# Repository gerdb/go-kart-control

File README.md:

#Go-Kart Control  
####Radio controlled displays for go-kart tracks  
---

##Install the Go-Kart-Control software
Download and unzip the ZIP archive containing all executables and also the source code:  
https://github.com/gerdb/go-kart-control/archive/master.zip  
On a windows system just start the executable **Go-Kart-Control.exe** in /install/win32 or win64  
On a Mac or Linux start the java JAR archive in install/all with **java - jar go-kart-control.jar**.  
Don't forget to set the correct serial port in settings.txt.  
Java must be installed: https://www.java.com/de/download/  

##Translation
You can translate the application.  
Open the *lang/messages.pot* file and translate it with http://poedit.net/  
Save the *messages_LANGUAGE_CODE.po* file in the *lang* folder of your program.  
Set the local code in *settings.txt*, if you don't want to use the system settings.

##Arduino software
If it's a new AVR, program it with the Arduino bootloader. For example with AVRDUDE:  
`avrdude -pm32u4 -cstk500 -P/dev/ttyUSB0 -e`  
`avrdude -pm32u4 -cstk500 -P/dev/ttyUSB0 -v -e -U lfuse:w:0xff:m -U hfuse:w:0xd8:m -U efuse:w:0xcb:m`  
`avrdude -pm32u4 -cstk500 -P/dev/ttyUSB0 -v -e -U flash:w:Caterina-Micro.hex -U lock:w:0x2F:m`

The Arduino project file is: **arduino/go_kart_panel/go_kart_panel.ino**

##Hardware setup
The PCB can be assembles in 2 variants: As a master module or as a panel module.  
The master module is connected to the PC.  
The panel module has a display.
The differences between both electronics are marked here:  

###PCB layout

###Master module
The master module is connected to a USB port of a PC or notebook. The master module can be supplied by USB or by an external 12V power supply. An external power supply is recommended on high power settings (If not, the blue LED is flickering). 

###Panel module
If there is a new master module, update the radio.ino file with the master's XBee address and download it to all panel modules. The panels will only accept data from this master.   
On startup, the software version, the battery voltage (120=12V) and the power setting (0..4) is displayed.  
The XBee module is ready when all LEDs blink for a short time.  
If then the testpoint P11 and P12 are connected together, the module displays the XBee address step by step and a display test is performed. Use this address to update the **settings.txt**  

Use 7-segment displays with common anode. Voltage is 12V. Use external resistors in each line **a**..**g**  
Connect LEDs to display the flag status. Connect the anode together.  
The maximum current for 7-segment display or LED is 300mA per line.

##Your own Go-Kart track
You can use the /pics/track.svg to generate you own background images for your go-kart tracks.  
Edit this with Inkscape https://inkscape.org/de/ and export it as bitmap to your /pics folder. Filename is background.png.  
Edit the settings.txt and change the x and y position of your panels.

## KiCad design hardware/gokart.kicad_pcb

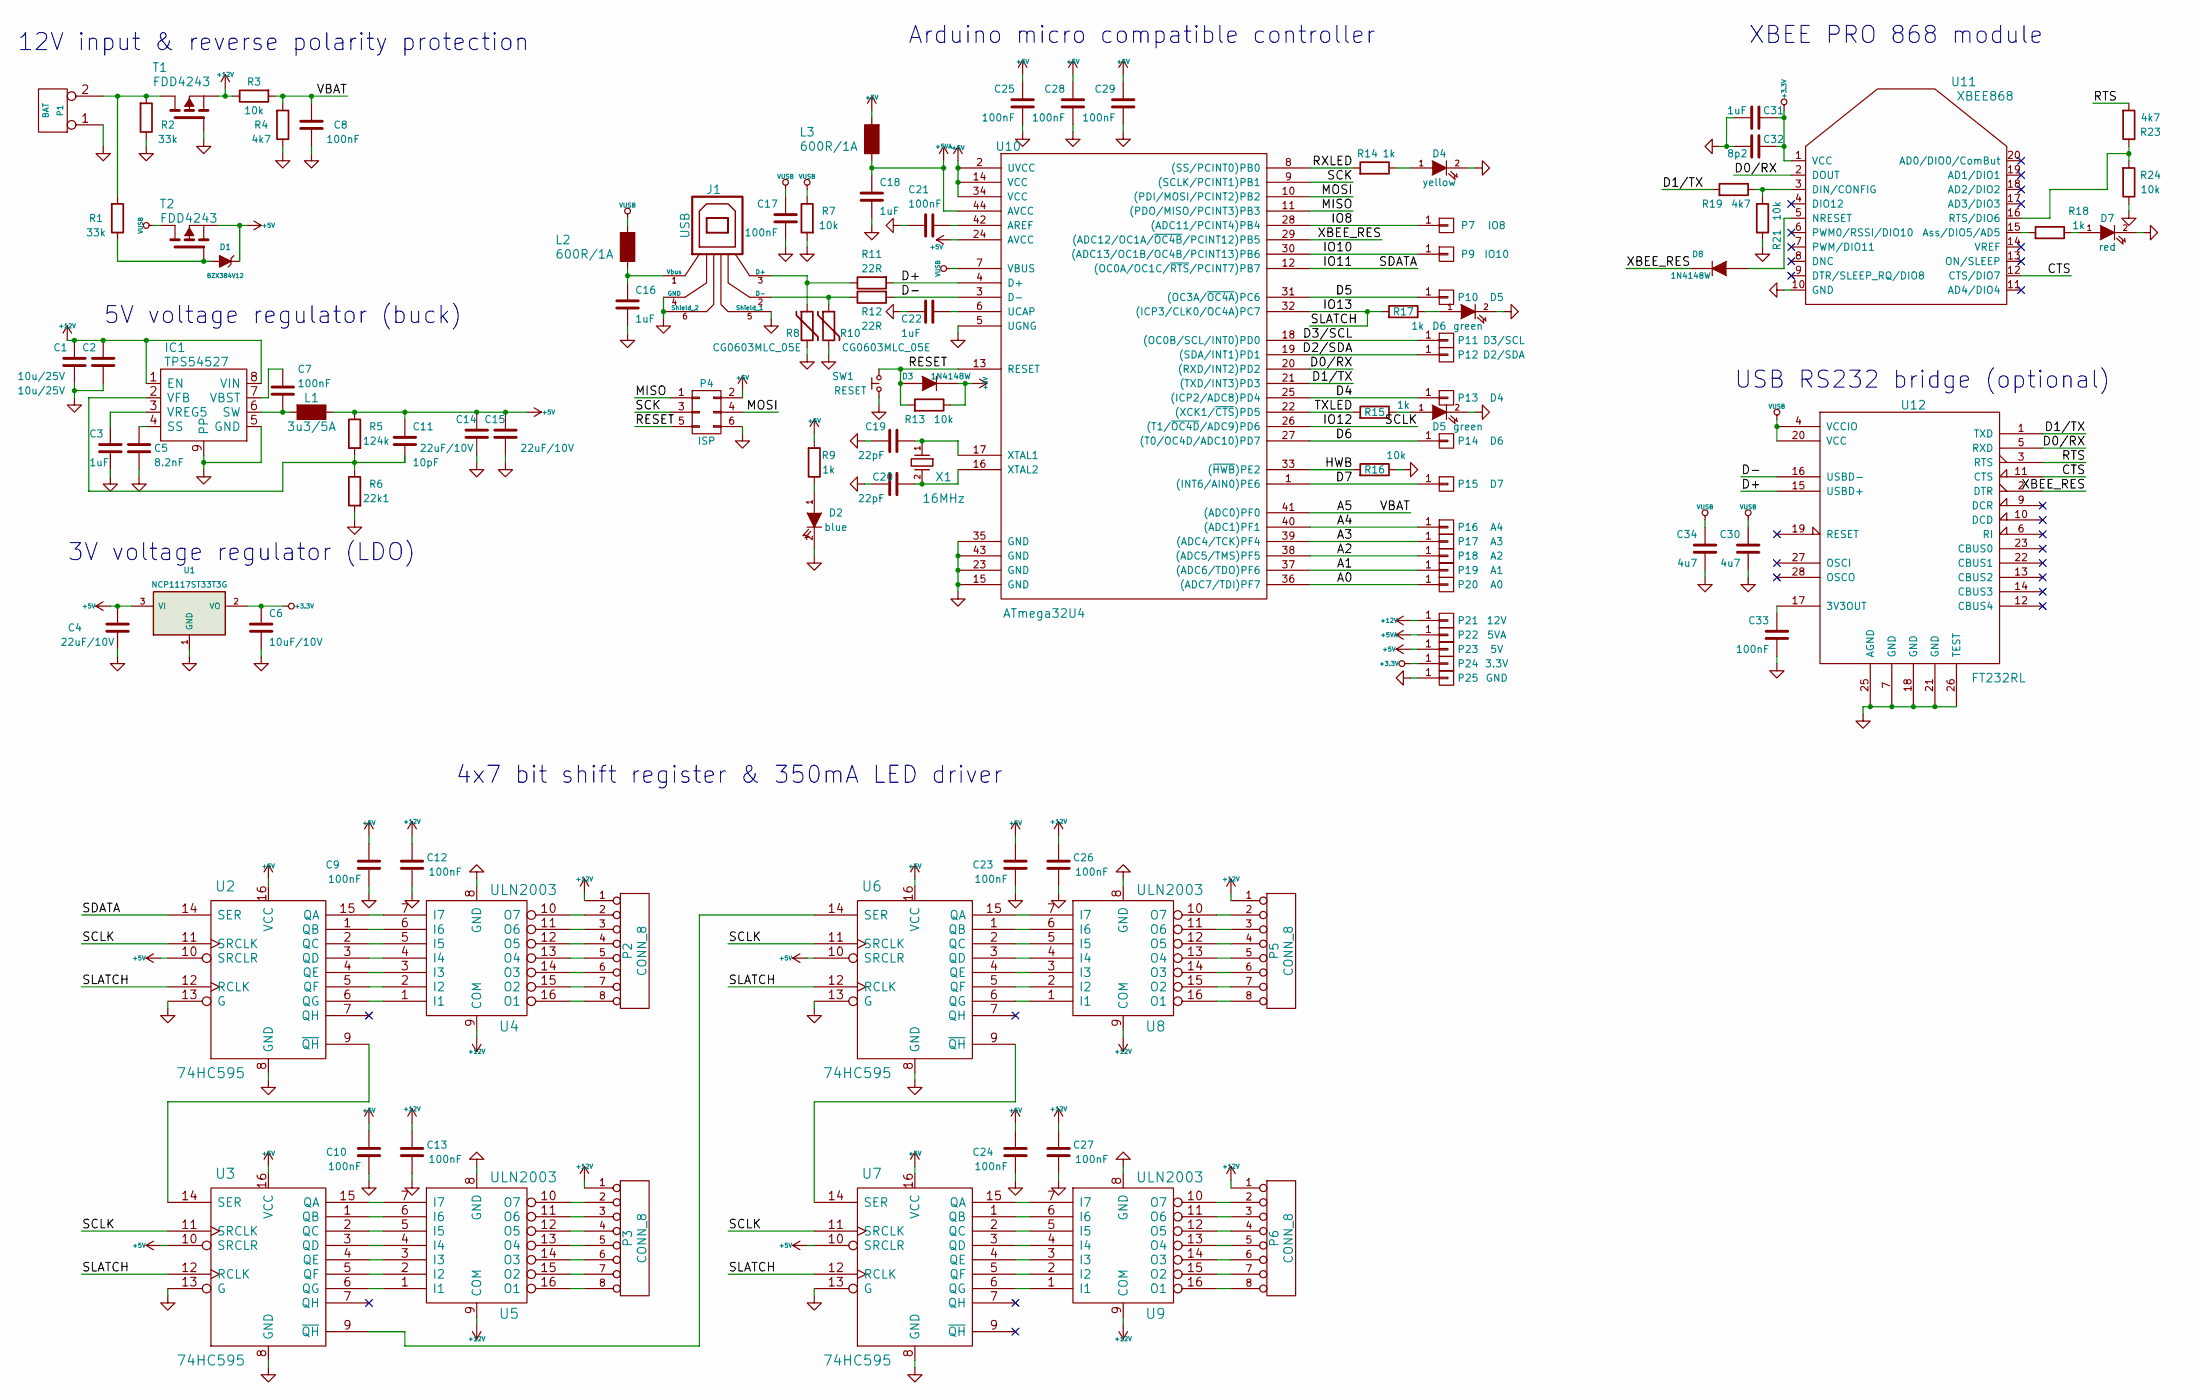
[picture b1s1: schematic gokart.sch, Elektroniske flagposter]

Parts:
C1, C2: 10u/25V; SMD-1210
C3, C16, C18, C22, C31: 1uF; SMD-0805
C4, C14, C15: 22uF/10V; SMD-1210
C5: 8.2nF; SMD-0805
C6: 10uF/10V; SMD-0805
C7, C8, C9, C10, C12, C13, C17, C21, C23, C24, C25, C26, C27, C28, C29, C33: 100nF; SMD-0805
C11: 10pF; SMD-0805
C19, C20: 22pF; SMD-0805
C30, C34: 4u7; SMD-0805
C32: 8p2; SMD-0805
D1: BZX384V12; SOD-323
D2: blue; LED-0805
D3, D8: 1N4148W; SOD-123
D4: yellow; LED-0805
D5, D6: green; LED-0805
D7: red; LED-0805
IC1: TPS54527; SOIC-8-N-1EP
J1: USB; USB_B
L1: 3u3/5A; L_XAL4030
L2, L3: 600R/1A; R_0805
P1: BAT; LP_KLEMME_5.08_2
P2, P3, P5, P6: CONN_8; RIA_8_3.5_TYP59
P4: ISP; Pin_Header_Straight_2x03
P7: IO8; Pin_Header_Straight_1x01
P9: IO10; Pin_Header_Straight_1x01
P10: D5; Pin_Header_Straight_1x01
P11: D3/SCL; Pin_Header_Straight_1x01
P12: D2/SDA; Pin_Header_Straight_1x01
P13: D4; Pin_Header_Straight_1x01
P14: D6; Pin_Header_Straight_1x01
P15: D7; Pin_Header_Straight_1x01
P16: A4; Pin_Header_Straight_1x01
P17: A3; Pin_Header_Straight_1x01
P18: A2; Pin_Header_Straight_1x01
P19: A1; Pin_Header_Straight_1x01
P20: A0; Pin_Header_Straight_1x01
P21: 12V; Pin_Header_Straight_1x01
P22: 5VA; Pin_Header_Straight_1x01
P23: 5V; Pin_Header_Straight_1x01
P24: 3.3V; Pin_Header_Straight_1x01
P25: GND; Pin_Header_Straight_1x01
R1, R2: 33k; R_0805
R3, R7, R13, R16, R21, R24: 10k; R_0805
R4, R19, R23: 4k7; R_0805
R5: 124k; R_0805
R6: 22k1; R_0805
R8, R10: CG0603MLC_05E; SMD-0603
R9, R14, R15, R17, R18: 1k; R_0805
R11, R12: 22R; R_0805
SW1: RESET; SW_PUSH_SMALL
T1, T2: FDD4243; DPAK-3_GDS
U1: NCP1117ST33T3G; DPAK-3
U2, U3, U6, U7: 74HC595; SO-16-N
U4, U5, U8, U9: ULN2003; SO-16-N
U10: ATmega32U4; TQFP-44
U11: XBEE868; XBEE_PRO_868
U12: FT232RL; SSOP-28
X1: 16MHz; Crystal_SMD_0603_2Pads_obsolete

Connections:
+3.3V: C6.1, C31.1, C32.1, P24.1, U1.2 (VO), U11.1 (VCC)
+5V: C4.1, C9.2, C10.2, C11.1, C14.1, C15.1, C23.2, C24.2, C25.2, C28.2, C29.2, D1.2 (K), D3.2 (K), L1.2, L3.1, P4.2, P23.1, R5.2, R9.1, R13.2, T2.S, U1.3 (VI), U2.10 (SRCLR), U2.16 (VCC), U3.10 (SRCLR), U3.16 (VCC), U6.10 (SRCLR), U6.16 (VCC), U7.10 (SRCLR), U7.16 (VCC), U10.2 (UVCC), U10.14 (VCC), U10.24 (AVCC), U10.34 (VCC)
+5VA: C18.1, L3.2, P22.1, U10.44 (AVCC)
+12V: C1.1, C2.1, C12.2, C13.2, C26.2, C27.2, IC1.1 (EN), IC1.8 (VIN), P2.1, P3.1, P5.1, P6.1, P21.1, R3.2, T1.S, U4.9 (COM), U5.9 (COM), U8.9 (COM), U9.9 (COM)
/A0: P20.1, U10.36 ((ADC7/TDI)PF7)
/A1: P19.1, U10.37 ((ADC6/TDO)PF6)
/A2: P18.1, U10.38 ((ADC5/TMS)PF5)
/A3: P17.1, U10.39 ((ADC4/TCK)PF4)
/A4: P16.1, U10.40 ((ADC1)PF1)
/A5: C8.1, R3.1, R4.1, U10.41 ((ADC0)PF0)
/CTS: U11.12 (CTS/DIO7), U12.11 (CTS)
/D0/RX: U10.20 ((RXD/INT2)PD2), U11.2 (DOUT), U12.5 (RXD)
/D1/TX: R19.1, U10.21 ((TXD/INT3)PD3), U12.1 (TXD)
/D2/SDA: P12.1, U10.19 ((SDA/INT1)PD1)
/D3/SCL: P11.1, U10.18 ((OC0B/SCL/INT0)PD0)
/D4: P13.1, U10.25 ((ICP2/ADC8)PD4)
/D5: P10.1, U10.31 ((OC3A/~OC4A~)PC6)
/D6: P14.1, U10.27 ((T0/OC4D/ADC10)PD7)
/D7: P15.1, U10.1 ((INT6/AIN0)PE6)
/D+: R11.1, U10.4 (D+), U12.15 (USBD+)
/D-: R12.1, U10.3 (D-), U12.16 (USBD-)
/HWB: R16.1, U10.33 ((~HWB~)PE2)
/IO8: P7.1, U10.28 ((ADC11/PCINT4)PB4)
/IO10: P9.1, U10.30 ((ADC13/OC1B/OC4B/PCINT13)PB6)
/IO11: U2.14 (SER), U10.12 ((OC0A/OC1C/~RTS~/PCINT7)PB7)
/IO12: U2.11 (SRCLK), U3.11 (SRCLK), U6.11 (SRCLK), U7.11 (SRCLK), U10.26 ((T1/~OC4D~/ADC9)PD6)
/IO13: R17.1, U2.12 (RCLK), U3.12 (RCLK), U6.12 (RCLK), U7.12 (RCLK), U10.32 ((ICP3/CLK0/OC4A)PC7)
/MISO: P4.1, U10.11 ((PDO/MISO/PCINT3)PB3)
/MOSI: P4.4, U10.10 ((PDI/MOSI/PCINT2)PB2)
/RESET: D3.1 (A), P4.5, R13.1, SW1.2, U10.13 (RESET)
/RTS: R23.1, U12.3 (RTS)
/RXLED: R14.1, U10.8 ((SS/PCINT0)PB0)
/SCK: P4.3, U10.9 ((SCLK/PCINT1)PB1)
/TXLED: R15.1, U10.22 ((XCK1/~CTS~)PD5)
/XBEE_RES: D8.2 (K), U10.29 ((ADC12/OC1A/~OC4B~/PCINT12)PB5), U12.2 (DTR)
GND: C1.2, C2.2, C3.2, C4.2, C5.2, C6.2, C8.2, C9.1, C10.1, C12.1, C13.1, C14.2, C15.2, C16.2, C17.1, C18.2, C19.2, C20.2, C21.2, C22.2, C23.1, C24.1, C25.1, C26.1, C27.1, C28.1, C29.1, C30.1, C31.2, C32.2, C33.1, C34.1, D2.2 (K), D4.2 (K), D5.2 (K), D6.2 (K), D7.2 (K), IC1.5 (GND), IC1.9 (PP), J1.4 (GND), J1.5 (Shield_1), J1.6 (Shield_2), P1.1, P4.6, P25.1, R2.2, R4.2, R6.1, R7.1, R8.2, R10.2, R16.2, R21.2, R24.2, SW1.1, T1.G, U1.1 (GND), U2.8 (GND), U2.13 (G), U3.8 (GND), U3.13 (G), U4.8 (GND), U5.8 (GND), U6.8 (GND), U6.13 (G), U7.8 (GND), U7.13 (G), U8.8 (GND), U9.8 (GND), U10.5 (UGNG), U10.15 (GND), U10.23 (GND), U10.35 (GND), U10.43 (GND), U11.10 (GND), U12.7 (GND), U12.18 (GND), U12.21 (GND), U12.25 (AGND), U12.26 (TEST)
unnamed: C3.1, IC1.3 (VREG5)
unnamed: C5.1, IC1.4 (SS)
unnamed: C7.1, IC1.7 (VBST)
unnamed: C7.2, IC1.6 (SW), L1.1
unnamed: C11.2, IC1.2 (VFB), R5.1, R6.2
unnamed: C16.1, J1.1 (Vbus), L2.2
unnamed: C19.1, U10.17 (XTAL1), X1.1
unnamed: C20.1, U10.16 (XTAL2), X1.2
unnamed: C21.1, U10.42 (AREF)
unnamed: C22.1, U10.6 (UCAP)
unnamed: C33.2, U12.17 (3V3OUT)
unnamed: D1.1 (A), R1.2, T2.G
unnamed: D2.1 (A), R9.2
unnamed: D4.1 (A), R14.2
unnamed: D5.1 (A), R15.2
unnamed: D6.1 (A), R17.2
unnamed: D7.1 (A), R18.2
unnamed: D8.1 (A), U11.5 (NRESET)
unnamed: J1.2 (D-), R10.1, R12.2
unnamed: J1.3 (D+), R8.1, R11.2
unnamed: P1.2 (PM), R1.1, R2.1, T1.D
unnamed: P2.2, U4.10 (O7)
unnamed: P2.3, U4.11 (O6)
unnamed: P2.4, U4.12 (O5)
unnamed: P2.5, U4.13 (O4)
unnamed: P2.6, U4.14 (O3)
unnamed: P2.7, U4.15 (O2)
unnamed: P2.8, U4.16 (O1)
unnamed: P3.2, U5.10 (O7)
unnamed: P3.3, U5.11 (O6)
unnamed: P3.4, U5.12 (O5)
unnamed: P3.5, U5.13 (O4)
unnamed: P3.6, U5.14 (O3)
unnamed: P3.7, U5.15 (O2)
unnamed: P3.8, U5.16 (O1)
unnamed: P5.2, U8.10 (O7)
unnamed: P5.3, U8.11 (O6)
unnamed: P5.4, U8.12 (O5)
unnamed: P5.5, U8.13 (O4)
unnamed: P5.6, U8.14 (O3)
unnamed: P5.7, U8.15 (O2)
unnamed: P5.8, U8.16 (O1)
unnamed: P6.2, U9.10 (O7)
unnamed: P6.3, U9.11 (O6)
unnamed: P6.4, U9.12 (O5)
unnamed: P6.5, U9.13 (O4)
unnamed: P6.6, U9.14 (O3)
unnamed: P6.7, U9.15 (O2)
unnamed: P6.8, U9.16 (O1)
unnamed: R18.1, U11.15 (Ass/DIO5/AD5)
unnamed: R19.2, R21.1, U11.3 (DIN/CONFIG)
unnamed: R23.2, R24.1, U11.16 (RTS/DIO6)
unnamed: U2.1 (QB), U4.6 (I6)
unnamed: U2.2 (QC), U4.5 (I5)
unnamed: U2.3 (QD), U4.4 (I4)
unnamed: U2.4 (QE), U4.3 (I3)
unnamed: U2.5 (QF), U4.2 (I2)
unnamed: U2.6 (QG), U4.1 (I1)
unnamed: U2.9 (~QH), U3.14 (SER)
unnamed: U2.15 (QA), U4.7 (I7)
unnamed: U3.1 (QB), U5.6 (I6)
unnamed: U3.2 (QC), U5.5 (I5)
unnamed: U3.3 (QD), U5.4 (I4)
unnamed: U3.4 (QE), U5.3 (I3)
unnamed: U3.5 (QF), U5.2 (I2)
unnamed: U3.6 (QG), U5.1 (I1)
unnamed: U3.9 (~QH), U6.14 (SER)
unnamed: U3.15 (QA), U5.7 (I7)
unnamed: U6.1 (QB), U8.6 (I6)
unnamed: U6.2 (QC), U8.5 (I5)
unnamed: U6.3 (QD), U8.4 (I4)
unnamed: U6.4 (QE), U8.3 (I3)
unnamed: U6.5 (QF), U8.2 (I2)
unnamed: U6.6 (QG), U8.1 (I1)
unnamed: U6.9 (~QH), U7.14 (SER)
unnamed: U6.15 (QA), U8.7 (I7)
unnamed: U7.1 (QB), U9.6 (I6)
unnamed: U7.2 (QC), U9.5 (I5)
unnamed: U7.3 (QD), U9.4 (I4)
unnamed: U7.4 (QE), U9.3 (I3)
unnamed: U7.5 (QF), U9.2 (I2)
unnamed: U7.6 (QG), U9.1 (I1)
unnamed: U7.15 (QA), U9.7 (I7)
VUSB: C17.2, C30.2, C34.2, L2.1, R7.2, T2.D, U10.7 (VBUS), U12.4 (VCCIO), U12.20 (VCC)

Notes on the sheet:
12V input & reverse polarity protection
5V voltage regulator (buck)
3V voltage regulator (LDO)
Arduino micro compatible controller
XBEE PRO 868 module
USB RS232 bridge (optional)
4x7 bit shift register & 350mA LED driver

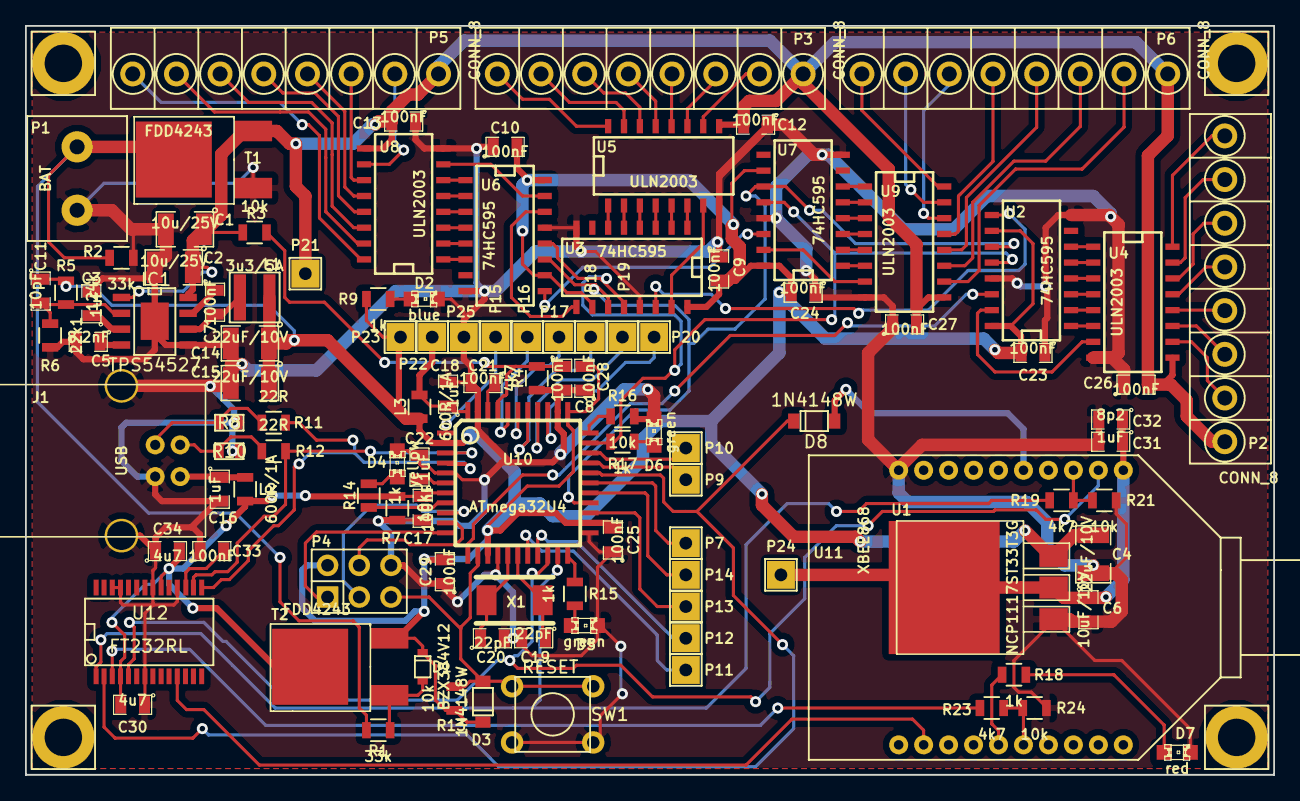
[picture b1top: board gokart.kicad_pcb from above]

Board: 2 copper layers, 100.0 x 60.0 mm, 113 parts (0 on the bottom side), 120 nets.

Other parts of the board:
HOLE_M3, HOLE_M3#2, HOLE_M3#3, HOLE_M3#4: VAL**; HOLE_M3

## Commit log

2014-11-07 1st Java project
2014-11-08 Added java sourc code
2014-11-08 Added splash image to readme
2014-11-08 Readme
2014-11-08 Changed directory structure Added hardware folder Added picture folder
2014-11-08 gitignore - Java
2014-11-08 Updated readme.md with some pictures
2014-11-09 Added comments and translated texts
2014-11-15 Adapted XBee API with purejavacomm
2014-11-16 Basic data exchange with XBee module. TX and RX. XBModule in echo mode.
2014-11-18 Signal strength indication and status of communication
2014-11-19 Close communication before exit Updated flags.png and background Removed some warnings
2014-11-20 Added some picture, improved error messages and new setting
2014-11-23 First arduino firmware
2014-11-24 Use of the arduino's shiftOut() function
2014-11-25 Arduino: Read the battery voltage and scale it to 0.1V
2014-11-26 Fix: Show RX indicator "no signal"
2014-11-26 Arduino: Undervoltage detection and timeout handling
2014-11-26 Arduino: new XBee radio module
2014-11-27 First complete exchange of data to the panel module and back.
2014-11-27 Bugfix: Setting power value
2014-11-29 Adruino V100: Set AP2 mode, accept only master frames, show own addr Updates settings.txt with 2 slave addresses
2014-11-30 Cycle timeout calculation
2014-11-30 Add install directory
2014-11-30 Create Win installers added 16x16 4bit icon changes settings.txt to Win line endings
2014-11-30 Added schematic files for both variants.
2014-11-30 Added panel diagram
2014-11-30 Updated project documentation
2014-12-07 Added test mode, voltage calibration and possibility to enable/disable pannels.
2014-12-07 Updated version to 1.1.0
2014-12-07 Enabled all modules
2014-12-07 Enabled panel 2
2014-12-07 Windows 32bit and 64bit files of versions 1.1.0
2014-12-07 runnable jar 1.1.0
2014-12-14 GUI Version 1.2.0 Arduino Version 003 Fix power setting for complete setup Resetting the XBee module after transmit timeout errors
2014-12-14 Updated language files
2014-12-14 Created Windows executable of V1.2.0
2014-12-14 Updated settings.txt in installation folders
2014-12-14 Updated the readme
2014-12-14 Updated hardware
2014-12-14 Updated readme with java link
